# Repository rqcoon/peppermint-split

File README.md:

# peppermint-split
split 4x10 keyboard, can double as a macropad

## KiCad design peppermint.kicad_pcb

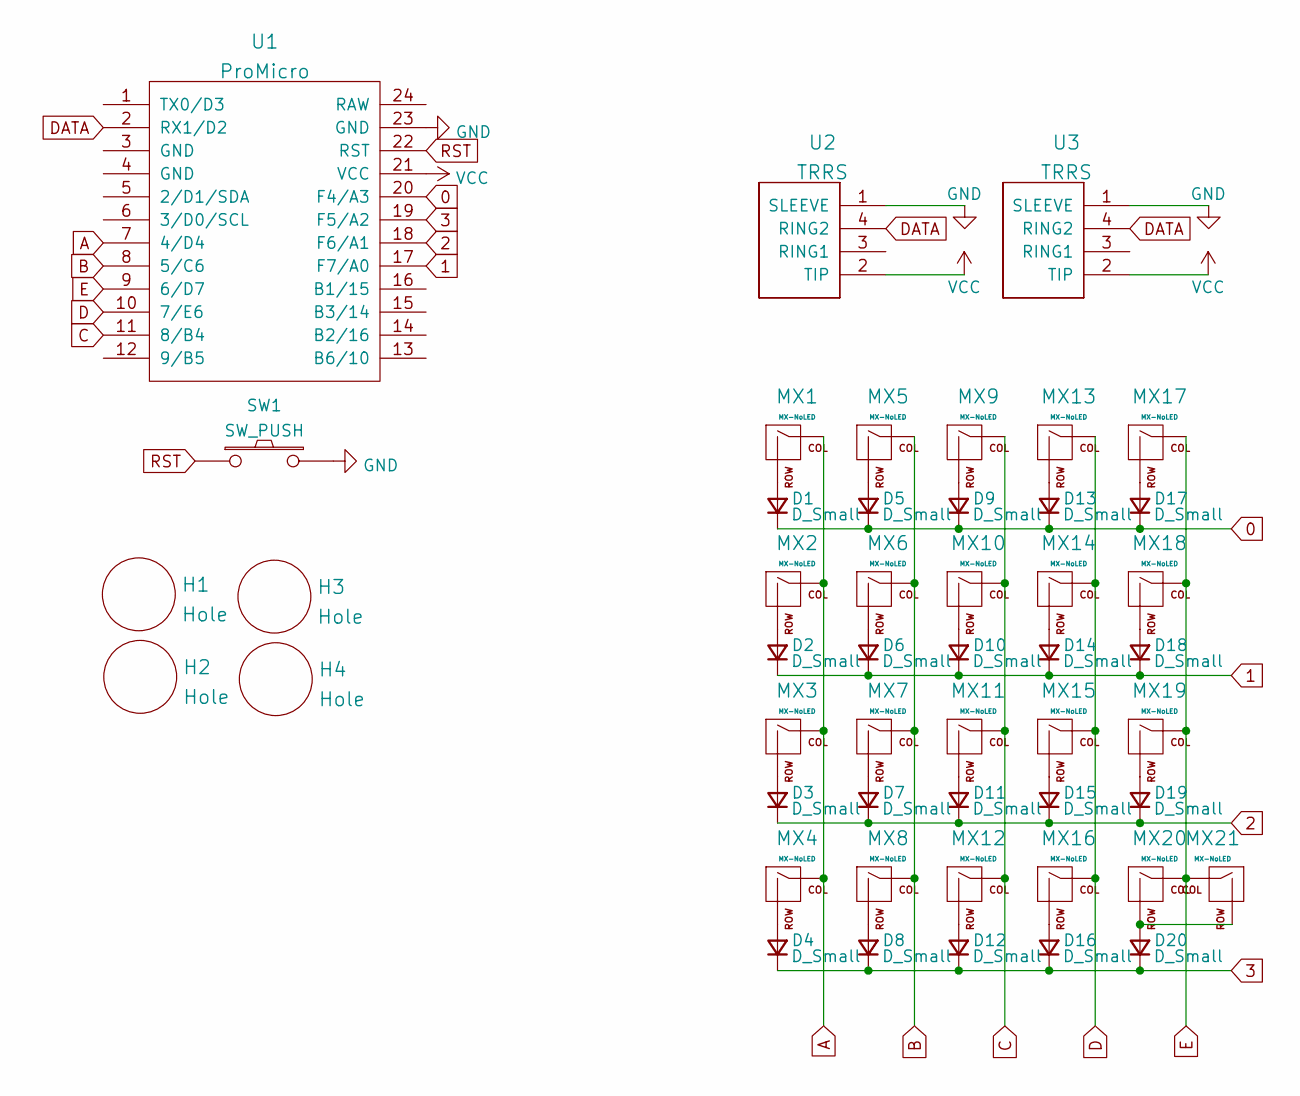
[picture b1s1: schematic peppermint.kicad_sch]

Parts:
D1, D2, D3, D4, D5, D6, D7, D8, D9, D10, D11, D12, D13, D14, D15, D16, D17, D18, D19, D20: D_Small; Diode-dual
H1, H2, H3, H4: Hole; HOLE_M3
MX1, MX2, MX3, MX4, MX5, MX6, MX7, MX8, MX9, MX10, MX11, MX12, MX13, MX14, MX15, MX16, MX17, MX18, MX19, MX20, MX21: MX-NoLED; SW_MX_reversible_minimal
SW1: SW_PUSH; SW_SPST_SKQG_WithStem
U1: ProMicro; ArduinoProMicro
U2, U3: TRRS; TRRS-PJ-320A

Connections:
0: D1.1 (K), D5.1 (K), D9.1 (K), D13.1 (K), D17.1 (K), U1.20 (F4/A3)
1: D2.1 (K), D6.1 (K), D10.1 (K), D14.1 (K), D18.1 (K), U1.17 (F7/A0)
2: D3.1 (K), D7.1 (K), D11.1 (K), D15.1 (K), D19.1 (K), U1.18 (F6/A1)
3: D4.1 (K), D8.1 (K), D12.1 (K), D16.1 (K), D20.1 (K), U1.19 (F5/A2)
A: MX1.1 (COL), MX2.1 (COL), MX3.1 (COL), MX4.1 (COL), U1.7 (4/D4)
B: MX5.1 (COL), MX6.1 (COL), MX7.1 (COL), MX8.1 (COL), U1.8 (5/C6)
C: MX9.1 (COL), MX10.1 (COL), MX11.1 (COL), MX12.1 (COL), U1.11 (8/B4)
D: MX13.1 (COL), MX14.1 (COL), MX15.1 (COL), MX16.1 (COL), U1.10 (7/E6)
DATA: U1.2 (RX1/D2), U2.4 (RING2), U3.4 (RING2)
E: MX17.1 (COL), MX18.1 (COL), MX19.1 (COL), MX20.1 (COL), MX21.1 (COL), U1.9 (6/D7)
GND: SW1.2, U1.23 (GND), U2.1 (SLEEVE), U3.1 (SLEEVE)
unnamed: D1.2 (A), MX1.2 (ROW)
unnamed: D2.2 (A), MX2.2 (ROW)
unnamed: D3.2 (A), MX3.2 (ROW)
unnamed: D5.2 (A), MX5.2 (ROW)
unnamed: D6.2 (A), MX6.2 (ROW)
unnamed: D7.2 (A), MX7.2 (ROW)
unnamed: D8.2 (A), MX8.2 (ROW)
unnamed: D9.2 (A), MX9.2 (ROW)
unnamed: D10.2 (A), MX10.2 (ROW)
unnamed: D11.2 (A), MX11.2 (ROW)
unnamed: D12.2 (A), MX12.2 (ROW)
unnamed: D13.2 (A), MX13.2 (ROW)
unnamed: D14.2 (A), MX14.2 (ROW)
unnamed: D15.2 (A), MX15.2 (ROW)
unnamed: D16.2 (A), MX16.2 (ROW)
unnamed: D17.2 (A), MX17.2 (ROW)
unnamed: D18.2 (A), MX18.2 (ROW)
unnamed: D19.2 (A), MX19.2 (ROW)
unnamed: D20.2 (A), MX20.2 (ROW), MX21.2 (ROW)
unnamed: D4.2 (A), MX4.2 (ROW)
RST: SW1.1, U1.22 (RST)
VCC: U1.21 (VCC), U2.2 (TIP), U3.2 (TIP)

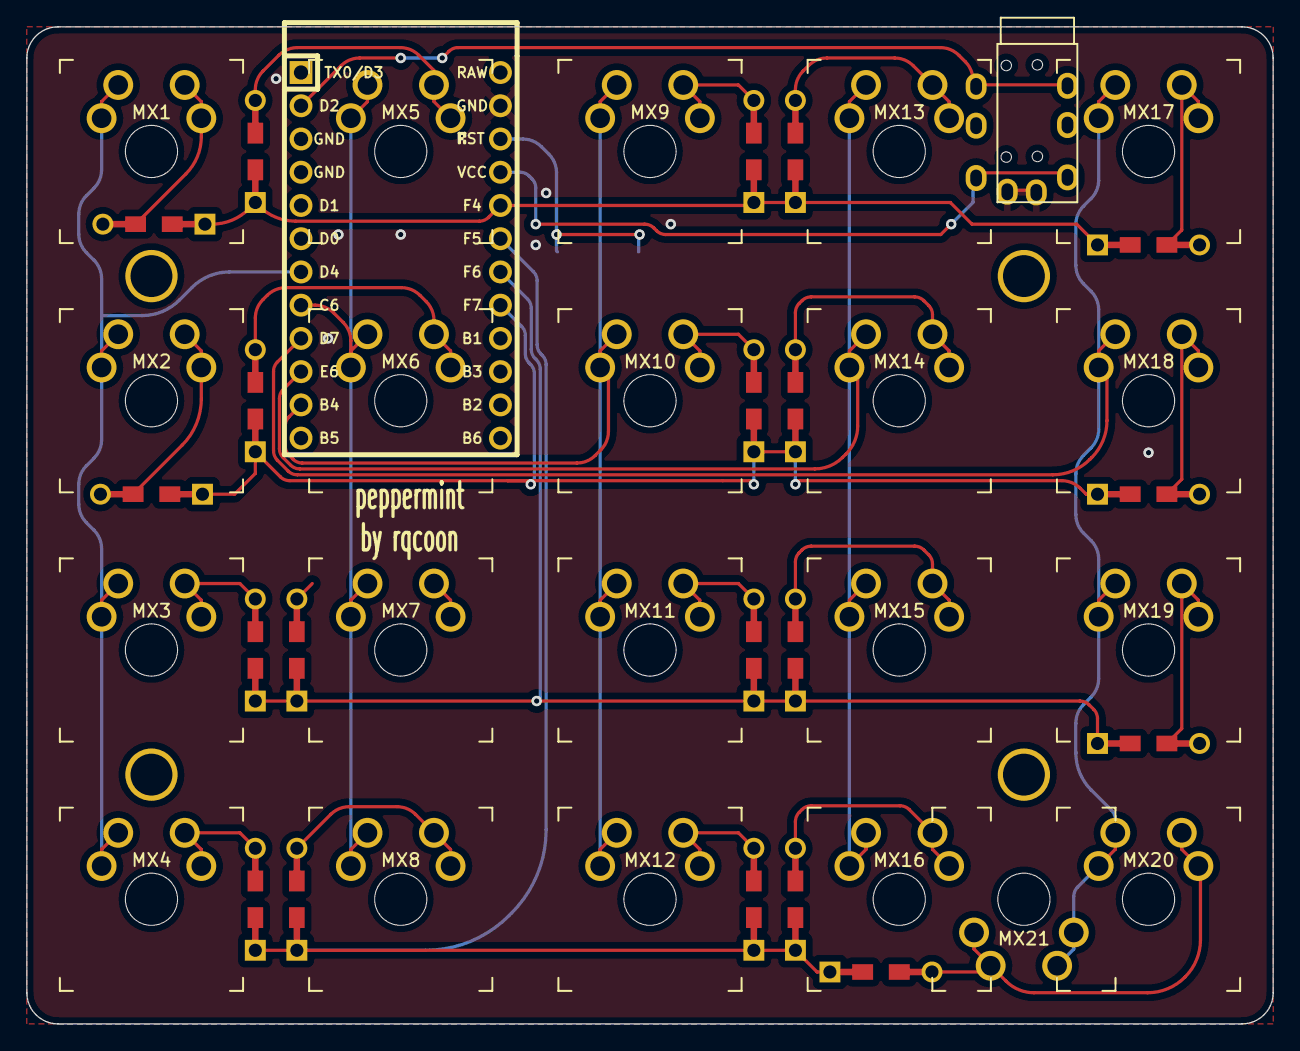
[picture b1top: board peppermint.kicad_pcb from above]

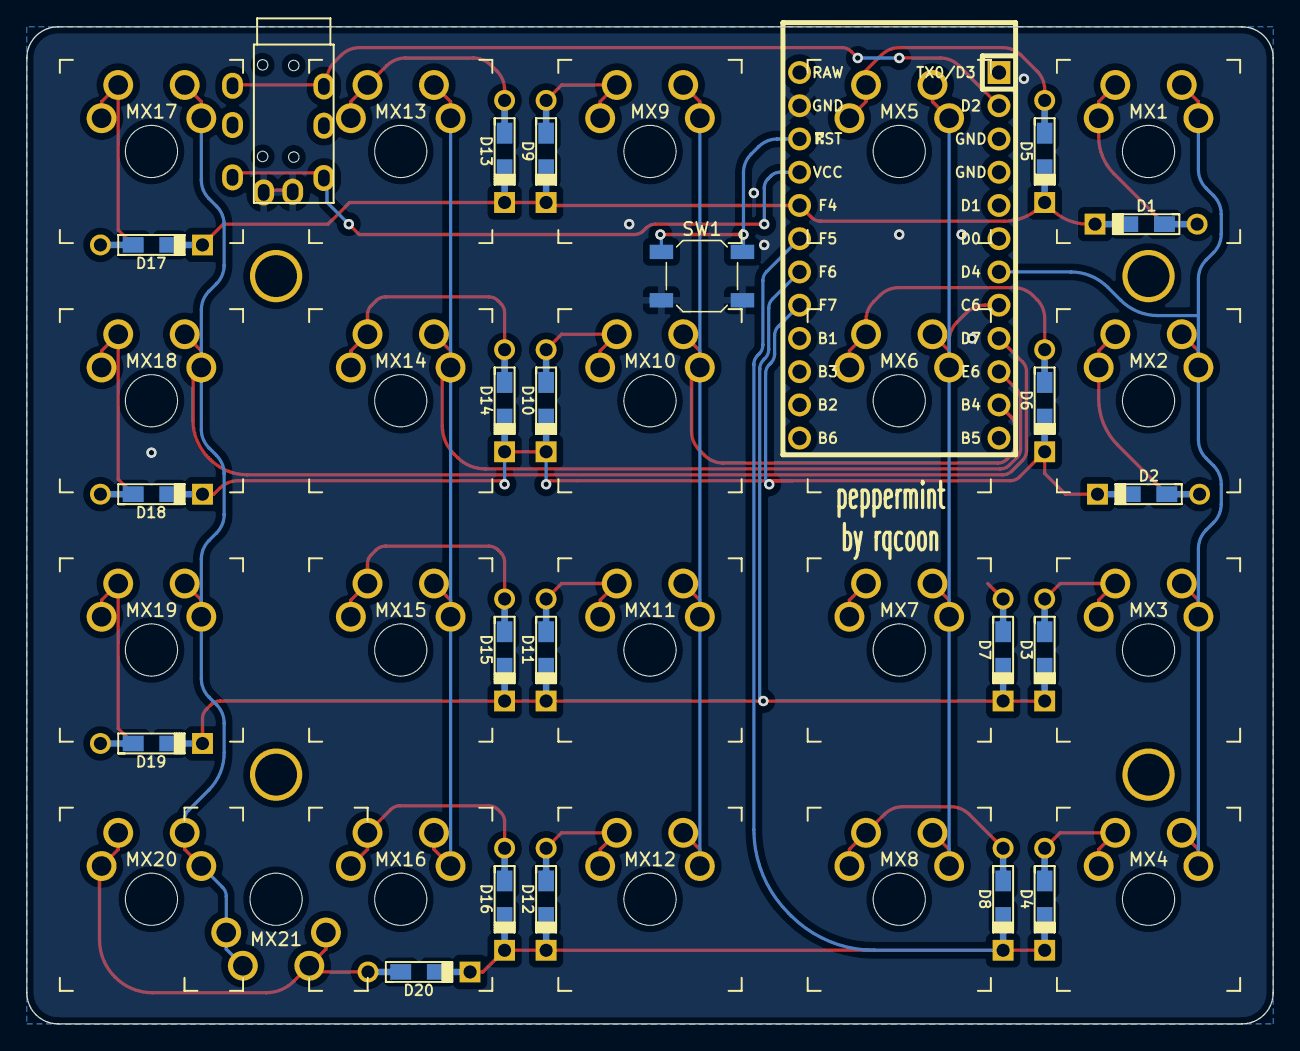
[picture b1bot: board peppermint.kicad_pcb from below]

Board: 2 copper layers, 95.2 x 76.2 mm, 49 parts (22 on the bottom side), 33 nets.

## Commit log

2021-12-08 Add Files
    Libs are not included
